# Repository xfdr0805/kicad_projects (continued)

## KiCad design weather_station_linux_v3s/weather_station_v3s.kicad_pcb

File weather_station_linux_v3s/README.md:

# weather_station_linux_v3s

##创建于2021.05.24

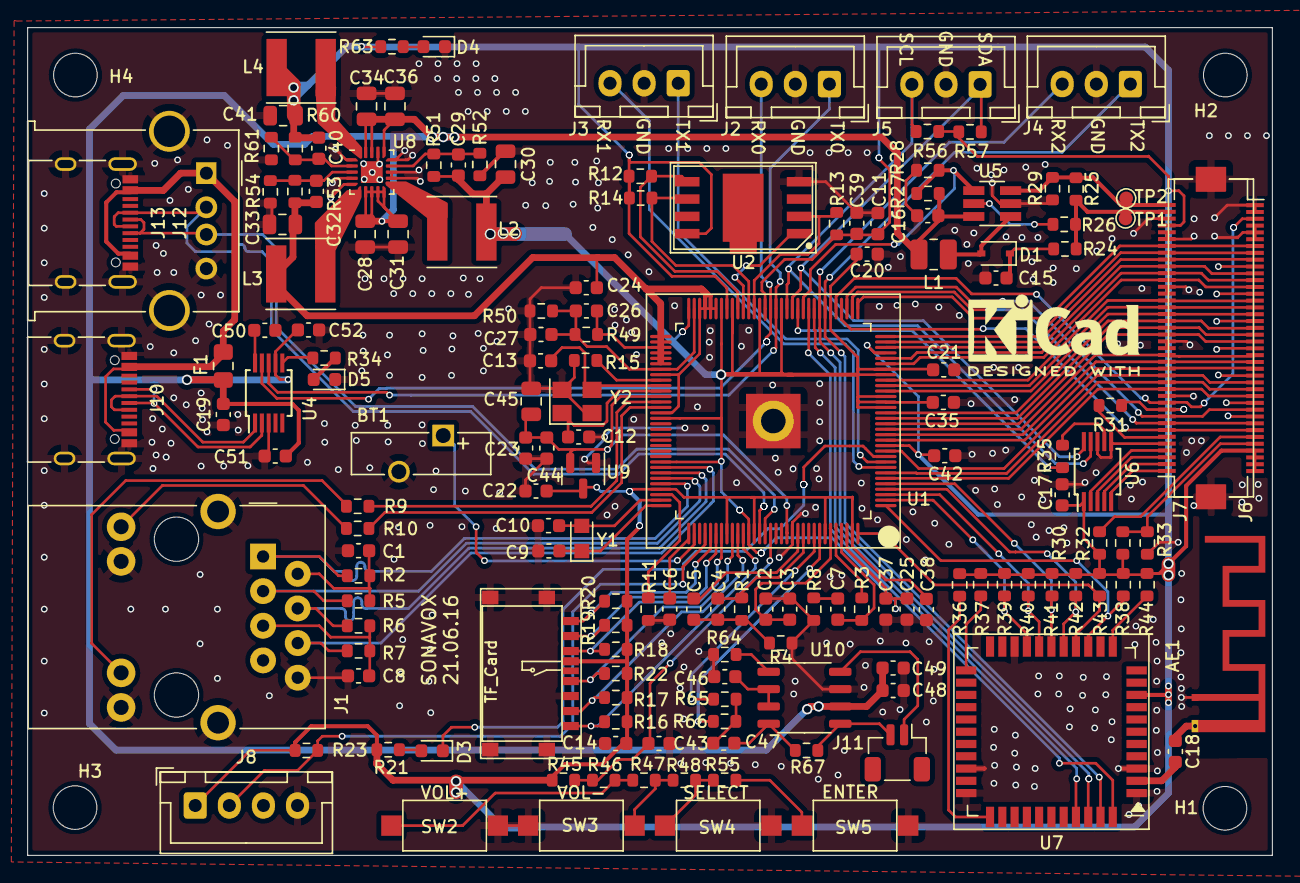
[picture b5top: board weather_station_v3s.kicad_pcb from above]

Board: 2 copper layers, 91.3 x 60.7 mm, 161 parts (0 on the bottom side), 131 nets.

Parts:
AE1: Antenna_Chip; Texas_SWRA117D_2.4GHz_Left
BT1: CR2032; Battery_Panasonic_CR1025-VSK_Vertical_CircularHoles
C1, C2, C7, C8, C11, C14, C26, C27, C43, C44, C46, C52: 0.1uF; C_0603_1608Metric
C3, C15, C16, C19, C49: 10uF; C_0603_1608Metric
C4, C6: 4.7uF; C_0603_1608Metric
C5, C17, C20, C21, C22, C23, C24, C25, C35, C37, C38, C39, C42, C47, C48, C50, C51: 1uF; C_0603_1608Metric
C9, C10: 10pF; C_0603_1608Metric
C12, C13: 12pF; C_0603_1608Metric
C18: 33pF; C_0603_1608Metric
C28, C30, C31, C33, C34, C36, C41, C45: 10uF; C_0805_2012Metric
C29, C32, C40: 18pF; C_0603_1608Metric
D1: 1N5819; D_SOD-323
D3, D4, D5: LED_Small; LED_0603_1608Metric
F1: 2A; Fuse_0805_2012Metric_Pad1.15x1.40mm_HandSolder
H1, H2, H3, H4: MountingHole_Pad; MountingHole_3.2mm_M3
J1: RJ45_Bel_SI-60062-F
J2: UART0; JST_XH_B3B-XH-A_1x03_P2.50mm_Vertical
J3: UART1; JST_XH_B3B-XH-A_1x03_P2.50mm_Vertical
J4: UART2; JST_XH_B3B-XH-A_1x03_P2.50mm_Vertical
J5: I2C0; JST_XH_B3B-XH-A_1x03_P2.50mm_Vertical
J6, J7: LCD_RGB_40P; Hirose_FH12-40S-0.5SH_1x40-1MP_P0.50mm_Horizontal
J8: DHT; JST_XH_B4B-XH-A_1x04_P2.50mm_Vertical
J10, J13: USB_C; USB_C_Receptacle_XKB_U262-16XN-4BVC11
J11: Audio; JST_SH_BM02B-SRSS-TB_1x02-1MP_P1.00mm_Vertical
J12: USB_A; USB_A_Molex_67643_Horizontal
L1: 2.2uH; L_1008_2520Metric
L2, L3, L4: 2.2uH; L_Taiyo-Yuden_MD-5050
R1, R53: 200K; R_0603_1608Metric
R2, R5, R6, R7: 49.9; R_0603_1608Metric
R3, R4, R24, R26, R35: 0R; R_0603_1608Metric
R8: 33R; R_0603_1608Metric
R9, R10, R21: 1K; R_0603_1608Metric
R11: 6K 1%; R_0603_1608Metric
R12, R13, R14, R16, R17, R18, R19, R20, R22, R23, R27, R30, R31, R32, R33, R37, R39, R40, R41, R42, R43, R44, R48, R56, R57: 10K; R_0603_1608Metric
R15: 240R; R_0603_1608Metric
R25: 120K; R_0603_1608Metric
R28: 1M; R_0603_1608Metric
R29: 4.7K; R_0603_1608Metric
R34, R49, R50, R63: 2K; R_0603_1608Metric
R36, R38, R45, R52, R54: 100K; R_0603_1608Metric
R46: 6.8K; R_0603_1608Metric
R47: 8.2K; R_0603_1608Metric
R51: 82.5K; R_0603_1608Metric
R55: 11K; R_0603_1608Metric
R60: 680K; R_0603_1608Metric
R61: 150K; R_0603_1608Metric
R64, R65, R66, R67: 20K; R_0603_1608Metric
SW2: VOL+; SW_SPST_CK_RS282G05A3
SW3: VOL-; SW_SPST_CK_RS282G05A3
SW4: SELECT; SW_SPST_CK_RS282G05A3
SW5: START; SW_SPST_CK_RS282G05A3
TP1: LED_OUT; TestPoint_Pad_D1.0mm
TP2: LED_FB; TestPoint_Pad_D1.0mm
U1: V3S; V3S_LQFP-128_14x14_Pitch0.4mm
U2: W25Q128JVS; WSON-8_8x6mm
U3: TF_Card; TF_Slot_Mini
U4: CH340E; MSOP-10_3x3mm_P0.5mm
U5: SY7201/SY7208ABC/LP3307; SOT-23-6_Handsoldering
U6: NS2009; MSOP-10_3x3mm_P0.5mm
U7: RTL8723BS_Module
U8: EA3036; QFN-20-1EP_3x3mm_P0.45mm_EP1.6x1.6mm
U9: XC6206PxxxMR; SOT-23
U10: LPA4890MSF; SOP-8_3.9x4.9mm_P1.27mm
Y1: 32.768KHz; Crystal_SMD_2012-2Pin_2.0x1.2mm_HandSoldering
Y2: 24MHz; Crystal_SMD_3225-4Pin_3.2x2.5mm

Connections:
+1V2: C20.2, C21.2, C25.1, C29.2, C30.2, C35.1, C37.1, L2.1, R51.1, U1.19 (VDD-SYS3), U1.20 (VDD-CPU3), U1.21 (VDD-CPU2), U1.25 (VDD-CPU1), U1.26 (VDD-CPU0), U1.38 (VDD-CPU4), U1.47 (VDD-CPU5), U1.51 (VDD-CPU6), U1.56 (VDD-CPU7), U1.58 (VDD-SYS4), U1.64 (VDD-SYS5), U1.80 (VDD-SYS0), U1.88 (EPHY-VDD), U1.108 (VDD-SYS1), U1.126 (VDD-SYS2)
+1V8: C24.2, C26.2, C32.2, C33.2, L3.1, R49.2, R53.1, U1.59 (VCC-DRAM8), U1.60 (VCC-DRAM9), U1.61 (VCC-DRAM10), U1.62 (VCC-DRAM11), U1.65 (VCC-DRAM0), U1.66 (VCC-DRAM1), U1.67 (VCC-DRAM2), U1.68 (VCC-DRAM3), U1.69 (VCC-DRAM4), U1.70 (VCC-DRAM5), U1.72 (VCC-DRAM6), U1.79 (VCC-DRAM7)
+3V0: C23.2, C44.2, C45.1, U1.76 (VCC-PLL), U1.115 (AVCC), U9.2 (VO)
+3V3: C11.1, C14.1, C17.1, C22.2, C38.1, C39.1, C40.2, C41.2, C42.1, J6.37 (VCC), J6.38 (VCC), J6.39 (VCC), J6.40 (VCC), J7.10 (DISP), J7.37 (VDD), J8.1, L4.1, R12.2, R13.2, R14.2, R16.2, R17.2, R18.2, R19.2, R20.2, R21.1, R22.1, R23.2, R30.1, R31.1, R32.1, R36.2, R37.1, R38.2, R39.1, R40.1, R41.1, R42.1, R43.1, R44.1, R45.2, R56.2, R57.2, R60.1, R63.1, U1.12 (VCC-PE0), U1.29 (VCC-PE1), U1.50 (VCC-IO3), U1.57 (VCC-IO2), U1.93 (EPHY-VCC), U1.104 (VCC-IO0), U1.109 (VCC-USB), U1.122 (HPVCCIN), U1.127 (VCC-IO1), U2.8 (VCC), U3.4 (VDD), U6.1 (VCC), U7.9 (VBAT), U9.3 (VI)
+5V: C16.2, C19.2, C28.2, C31.2, C34.2, C36.2, C48.2, C49.2, C51.1, C52.1, F1.2, L1.2, R27.1, U4.7 (VCC), U5.6 (IN), U8.7 (VIN2), U8.8 (EN2), U8.9 (EN1), U8.10 (VIN1), U8.16 (VCC), U8.18 (EN3), U8.19 (VIN3), U10.6 (VDD)
/Audio/HPOUT_L: R66.1, U1.121 (HPOUTL)
/Audio/HPOUT_R: R65.1, U1.120 (HPOUTR)
/CPU/EPHY_LINK_LED: R9.1, U1.77 (EPHY-LINK-LED)
/CPU/EPHY_RXN: J1.6 (RD-), R7.2, U1.89 (EPHY-RTN)
/CPU/EPHY_RXP: J1.4 (RD+), R6.2, U1.90 (EPHY-RXP)
/CPU/EPHY_SPD_LED: R10.1, U1.78 (EPHY-SPD-LED)
/CPU/EPHY_TXN: J1.3 (TD-), R5.2, U1.91 (EPHY-TXN)
/CPU/EPHY_TXP: J1.1 (TD+), R2.2, U1.92 (EPHY-TXP)
/CPU/GNDA: C4.1, C5.2, R1.2, R4.1
/CPU/HPCOM: C7.2, R3.1, U1.125 (HPCOM)
/CPU/HPCOMFB: R3.2, U1.124 (HPCOMFB)
/CPU/HPVCCBP: C2.2, C3.2, U1.123 (HPVCCBP)
/CPU/LCD_CLK: J6.3 (CK), J7.11 (DCLK), U1.37 (PE0/CSI_PCLK/LCD_CLK)
/CPU/LCD_D2: J6.7 (R0), J7.34 (R2), U1.33 (PE4/CSI_D0/LCD_D2)
/CPU/LCD_D3: J6.8 (R1), J7.33 (R3), U1.32 (PE5/CSI_D1/LCD_D3)
/CPU/LCD_D4: J6.9 (R2), J7.32 (R4), U1.31 (PE6/CSI_D2/LCD_D4)
/CPU/LCD_D5: J6.11 (R3), J7.31 (R5), U1.30 (PE7/CSI_D3/LCD_D5)
/CPU/LCD_D6: J6.12 (R4), J7.30 (R6), U1.28 (PE8/CSI_D4/LCD_D6)
/CPU/LCD_D7: J6.13 (R5), J7.29 (R7), U1.27 (PE9/CSI_D5/LCD_D7)
/CPU/LCD_D10: J6.15 (G0), J7.26 (G2), U1.24 (PE10/CSI_D6/LCD_D10)
/CPU/LCD_D11: J6.16 (G1), J7.25 (G3), U1.23 (PE11/CSI_D7/LCD_D11)
/CPU/LCD_D12: J6.17 (G2), J7.24 (G4), U1.22 (PE12/CSI_D8/LCD_D12)
/CPU/LCD_D13: J6.19 (G3), J7.23 (G5), U1.18 (PE13/CSI_D9/LCD_D13)
/CPU/LCD_D14: J6.20 (G4), J7.22 (G6), U1.17 (PE14/CSI_D10/LCD_D14)
/CPU/LCD_D15: J6.21 (G5), J7.21 (G7), U1.16 (PE15/CSI_D11/LCD_D15)
/CPU/LCD_D18: J6.23 (B0), J7.18 (B2), U1.15 (PE16/CSI_D12/LCD_D18)
/CPU/LCD_D19: J6.24 (B1), J7.17 (B3), U1.14 (PE17/CSI_D13/LCD_D19)
/CPU/LCD_D20: J6.25 (B2), J7.16 (B4), U1.13 (PE18/CSI_D14/LCD_D20)
/CPU/LCD_D21: J6.27 (B3), J7.15 (B5), U1.11 (PE19/CSI_D15/LCD_D21)
/CPU/LCD_D22: J6.28 (B4), J7.14 (B6), U1.7 (PE23/LCD_D22)
/CPU/LCD_D23: J6.29 (B5), J7.13 (B7), U1.6 (PE24/LCD_D23)
/CPU/LCD_DE: J6.34 (FGND), J7.7 (DE), U1.36 (PE1/CSI_MCLK/LCD_DE)
/CPU/LCD_HSYNC: J6.31 (Hsync), J7.9 (HSYNC), U1.35 (PE2/CSI_HSYNC/LCD_HSYNC)
/CPU/LCD_PWM: R27.2, R28.1, U1.43 (PB4/PWM0/PB_EINT4), U5.4 (EN)
/CPU/LCD_VSYNC: J6.33 (Vsync), J7.8 (VSYNC), U1.34 (PE3/CSI_VSYNC/LCD_VSYNC)
/CPU/LRADC: C43.1, R45.1, R46.1, U1.112 (LRADC0)
/CPU/PE20: D3.1 (K), U1.10 (PE20/CSI_FIELD/CSI_MIPI_MCLK)
/CPU/PF6: J8.2, R23.1, U1.100 (PF6)
/CPU/SDC0_CLK: R22.2, U1.105 (PF2/SDC0_CLK/UART0_TX), U3.5 (CLK)
/CPU/SDC0_CMD: R18.1, U1.103 (PF3/SDC0_CMD/JTAGDO1), U3.3 (CMD)
/CPU/SDC0_D0: R17.1, U1.106 (PF1/SDC0_D0/JTAG_DI1), U3.7 (DAT0)
/CPU/SDC0_D1: R16.1, U1.107 (PF0/SDC0_1/JTAG_MS1), U3.8 (DAT1)
/CPU/SDC0_D2: R20.1, U1.101 (PF5/SDC0_D2/JTAG_CK1), U3.1 (DAT2)
/CPU/SDC0_D3: R19.1, U1.102 (PF4/SDC0_D3/UART0_RX), U3.2 (DAT3/CD)
/CPU/SDC1_CLK: R41.2, U1.5 (PG0/SDC1_CLK/PG_EINT0), U7.17 (SDIO_CLK)
/CPU/SDC1_CMD: R42.2, U1.4 (PG1/SDC1_CMD/PG_EINT1), U7.16 (SDIO_CMD)
/CPU/SDC1_D0: R40.2, U1.3 (PG2/SDC1_D0/PG_EINT2), U7.18 (SDIO_D0)
/CPU/SDC1_D1: R39.2, U1.2 (PG3/SDC1_D1/PG_EINT3), U7.19 (SDIO_D1)
/CPU/SDC1_D2: R44.2, U1.1 (PG4/SDC1_D2/PG_EINT4), U7.14 (SDIO_D2)
/CPU/SDC1_D3: R43.2, U1.128 (PG5/SDC1_D3/PG_EINT5), U7.15 (SDIO_D3)
/CPU/SPI_CLK: R14.1, U1.53 (PC1/SDC2_CMD/SPI_CLK), U2.6 (CLK)
/CPU/SPI_CS: U1.54 (PC2/SDC2_RST/SPI_CS), U2.1 (~CS)
/CPU/SPI_MISO: R13.1, U1.52 (PC0/SDC2_CLK/SPI_MISO), U2.2 (DO(IO1))
/CPU/SPI_MOSI: R12.1, U1.55 (PC3/SDC2_D0/SPI_MOSI), U2.5 (DI(IO0))
/CPU/SZQ: R15.1, U1.73 (SZQ)
/CPU/TP_INIT: R35.2, U1.44 (PB5/PWM1/PB_EINT5)
/CPU/TWI0_SCK: J5.1, R57.1, U1.45 (PB6/TWI0_SCK/PB_EINT6), U6.10 (SCL)
/CPU/TWI0_SDA: J5.3, R56.1, U1.46 (PB7/TWI0_SDA/PB_EINT7), U6.9 (SDA)
/CPU/UART0_RX: J2.3, U1.49 (PB9/TWI1_SDA/UART0_RX/PB_EINT9), U4.9 (RXD)
/CPU/UART0_TX: J2.1, U1.48 (PB8/TWI1_SCK/UART0_TX/PB_EINT8), U4.8 (TXD)
/CPU/UART1_RX: J3.3, U1.8 (PE22/CSI_SDA/TWI1_SDA/UART1_RX)
/CPU/UART1_TX: J3.1, U1.9 (PE21/CSI_SCK/TWI1_SCK/UART1_TX)
/CPU/UART2_CTS: U1.42 (PB3/UART2_CTS/PB_EINT3), U7.44 (UART_CTS)
/CPU/UART2_RTS: U1.41 (PB2/UART2_RTS/PB_EINT2), U7.41 (UART_RTS)
/CPU/UART2_RX: J4.3, U1.40 (PB1/UART2_RX/PB_EINT1), U7.42 (UART_TXD)
/CPU/UART2_TX: J4.1, U1.39 (PB0/UART2_TX/PB_EINT0), U7.43 (UART_RXD)
/CPU/USB_D+: J12.3 (D+), J13.A6 (D+), J13.B6 (D+), U1.111 (USB-DP)
/CPU/USB_D-: J12.2 (D-), J13.A7 (D-), J13.B7 (D-), U1.110 (USB-DM)
/CPU/VRA1: C5.1, U1.117 (VRA1)
/CPU/VRA2: C4.2, R1.1, U1.118 (VRA2)
/LCD/LCD_LEDA: J7.39 (LEDA), R24.1, R25.2, R26.1, TP1.1
/LCD/LCD_LEDK: J7.40 (LEDK), R25.1, R29.2, TP2.1, U5.3 (FB)
/LCD/LCD_XL: J7.2 (XL), U6.4 (XN)
/LCD/LCD_XR: J7.4 (XR), U6.2 (XP)
/LCD/LCD_YB: J7.3 (YB), U6.3 (YP)
/LCD/LCD_YT: J7.1 (YT), U6.5 (YN)
GND: AE1.1 (FEED), BT1.2 (-), C1.1, C2.1, C3.1, C6.1, C8.1, C9.1, C10.1, C11.2, C12.1, C13.1, C14.2, C15.2, C16.1, C17.2, C19.1, C20.1, C21.1, C22.1, C23.1, C24.1, C25.2, C27.1, C28.1, C30.1, C31.1, C33.1, C34.1, C35.2, C36.1, C37.2, C38.2, C39.2, C41.1, C42.2, C43.2, C44.1, C45.2, C46.1, C48.1, C49.1, C50.2, C51.2, C52.2, D4.1 (K), D5.1 (K), J1.8 (GND), J1.L2 (LEDY_K), J1.L4 (LEDG_K), J1.SH (SHIELD), J2.2, J3.2, J4.2, J5.2, J6.1 (GND), J6.2 (GND), J6.4 (GND), J6.5 (GND), J6.6 (REF), J6.10 (GND), J6.14 (GND), J6.18 (GND), J6.22 (GND), J6.26 (GND), J6.30 (GND), J6.32 (GND), J6.MP, J7.5 (GND), J7.12 (GND), J7.19 (B1), J7.20 (B0), J7.27 (G1), J7.28 (G0), J7.35 (R1), J7.36 (R0), J7.38 (GND), J7.MP (MountPin), J8.4, J10.A1 (GND), J10.A12 (GND), J10.B1 (GND), J10.B12 (GND), J10.S1 (SHIELD), J12.4 (GND), J12.5 (Shield), J13.A1 (GND), J13.A12 (GND), J13.B1 (GND), J13.B12 (GND), J13.S1 (SHIELD), R4.2, R8.2, R11.2, R15.2, R28.2, R29.1, R33.2, R50.1, R52.2, R54.2, R61.2, R64.1, SW2.1, SW3.1, SW4.1, SW5.1, U1.116 (AGND), U1.129 (EGND), U2.4 (GND), U3.6 (VSS), U3.S (SHIELD), U4.3 (GND), U5.2 (GND), U6.6 (GND), U6.8 (A0), U7.1 (GND), U7.3 (GND), U7.20 (GND), U7.31 (GND), U7.33 (GND), U8.1 (GND3), U8.4 (GND2), U8.5 (GND2), U8.12 (GND1), U8.13 (GND1), U8.15 (AGND), U8.17 (AGND), U8.21 (EPAD), U9.1 (GND), U10.7 (GND), Y2.2, Y2.4
unnamed: AE1.2 (PCB_Trace), C18.2
unnamed: BT1.1 (+), U1.98 (VCC-RTC)
unnamed: C1.2, J1.2 (TCT), R2.1, R5.1
unnamed: C6.2, U1.97 (RTC-VIO)
unnamed: C7.1, R8.1
unnamed: C8.2, J1.5 (RCT), R6.1, R7.1
unnamed: C9.2, U1.96 (X32KIN), Y1.1
unnamed: C10.2, U1.95 (X32KOUT), Y1.2
unnamed: C12.2, U1.75 (X24MIN), Y2.1
unnamed: C13.2, U1.74 (X24MOUT), Y2.3
unnamed: C15.1, D1.1 (K), R24.2
unnamed: C18.1, U7.2 (WIFI/BT_ANT)
unnamed: C29.1, R51.2, R52.1, U8.14 (FB1)
unnamed: C32.1, R53.2, R54.1, U8.3 (FB2)
unnamed: C40.1, R60.2, R61.1, U8.2 (FB3)
unnamed: C46.2, U10.2 (BYPASS), U10.3 (IN+)
unnamed: C47.1, R65.2, R66.2
unnamed: C47.2, R67.1, U10.4 (IN-)
unnamed: C50.1, U4.10 (V3)
unnamed: D1.2 (A), L1.1, U5.1 (SW)
unnamed: D3.2 (A), R21.2
unnamed: D4.2 (A), R63.2
unnamed: D5.2 (A), R34.2
unnamed: F1.1, J10.A4 (VBUS), J10.A9 (VBUS), J10.B4 (VBUS), J10.B9 (VBUS), J12.1 (VBUS), J13.A4 (VBUS), J13.A9 (VBUS), J13.B4 (VBUS), J13.B9 (VBUS)
unnamed: J1.L1 (LEDY_A), R10.2
unnamed: J1.L3 (LEDG_A), R9.2
unnamed: J6.35 (ENABLE), R30.2
unnamed: J6.36 (Mode), R32.2, R33.1
unnamed: J7.6 (NC/PSSEL), R31.2
unnamed: J10.A6 (D+), J10.B6 (D+), U4.1 (UD+)
unnamed: J10.A7 (D-), J10.B7 (D-), U4.2 (UD-)
unnamed: J11.1, U10.8 (VO2(+))
unnamed: J11.2, R67.2, U10.5 (VO1(-))
unnamed: L2.2, U8.11 (LX1)
unnamed: L3.2, U8.6 (LX2)
unnamed: L4.2, U8.20 (LX3)
unnamed: R11.1, U1.94 (EPHY-RTX)
unnamed: R26.2, U5.5 (OV)
unnamed: R34.1, U4.6 (TNOW)
unnamed: R35.1, U6.7 (PENIRQ)
unnamed: R36.1, U7.34 (~BT_RST)
unnamed: R37.2, U7.23 (VIN_LDO)
unnamed: R38.1, U7.12 (WL_REG)
unnamed: R46.2, R47.1, SW2.2
unnamed: R47.2, R48.1, SW3.2
unnamed: R48.2, R55.1, SW4.2
unnamed: R55.2, SW5.2
unnamed: R64.2, U10.1 (~SHDN)
SVREF: C26.1, C27.2, R49.1, R50.2, U1.63 (SVREF1), U1.71 (SVREF0)

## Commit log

2021-07-08 Initial commit kicad工程统一由git管理
